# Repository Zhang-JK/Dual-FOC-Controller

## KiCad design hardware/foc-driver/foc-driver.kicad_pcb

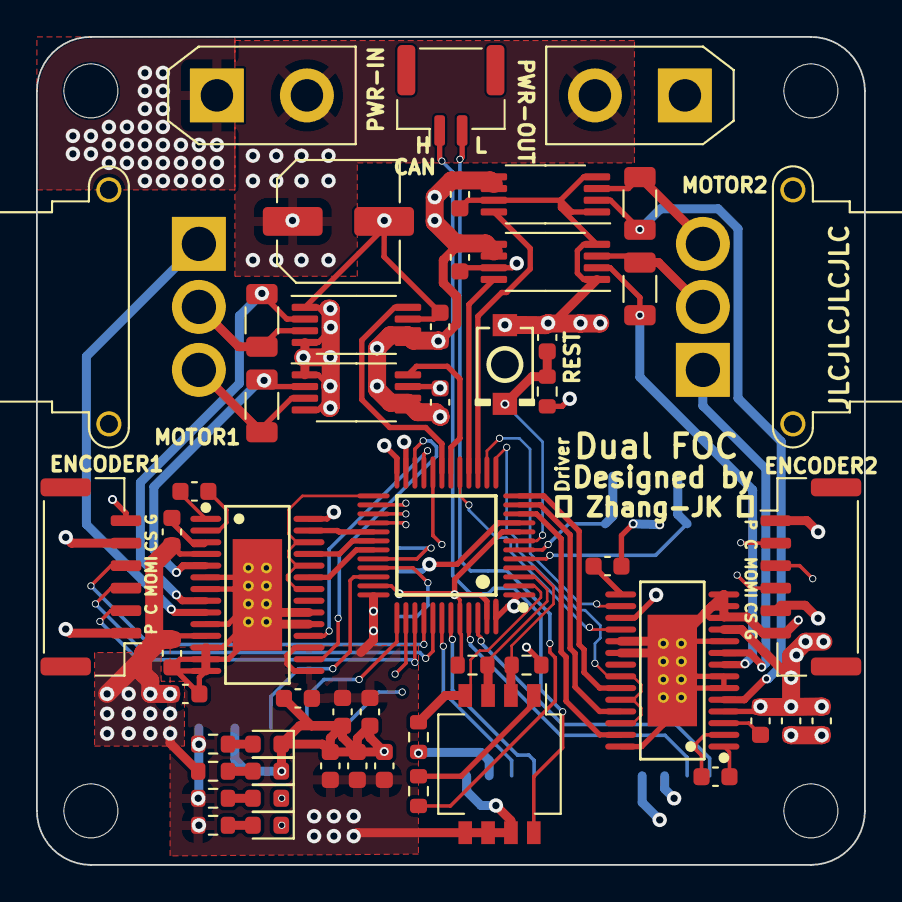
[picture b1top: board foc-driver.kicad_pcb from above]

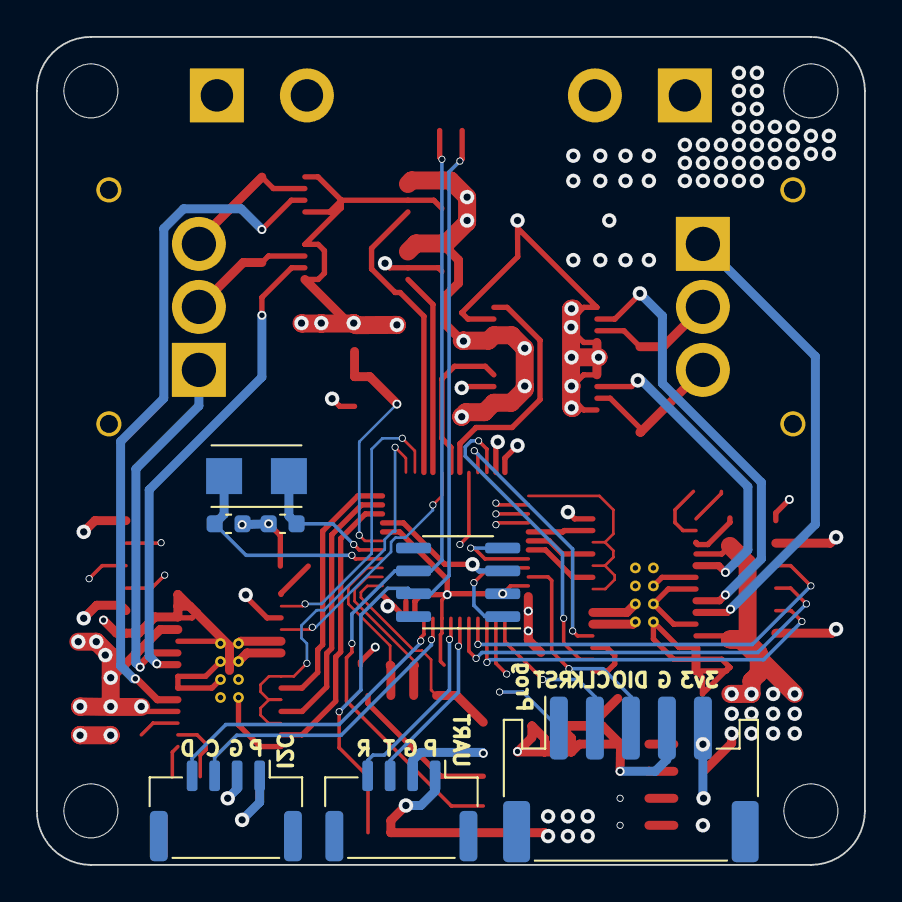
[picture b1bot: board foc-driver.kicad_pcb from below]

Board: 4 copper layers, 46.0 x 46.0 mm, 65 parts (7 on the bottom side), 65 nets.

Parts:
C1, C2, C3, C4, C7, C8, C9, C10, C12, C13, C18, C19, C20, C21: 0.1uF; C_0603_1608Metric
C5, C6: 0.01uF; C_0603_1608Metric
C11: 10uF; C_0603_1608Metric
C14, C15: 0.47uF; C_0603_1608Metric
C16, C17: 36pF; C_0603_1608Metric
C22: 100uF; C_Elec_6.3x7.7
C23: 0.1uf; C_0603_1608Metric
D2, D3: LED-R; LED_0603_1608Metric
D4: LED-B; LED_0603_1608Metric
D5: LED-G; LED_0603_1608Metric
H1, H2, H3, H4: MountingHole; MountingHole_3mm
J1: OUT1; AMASS_MR30PW-FB_1x03_P3.50mm_Horizontal
J2: OUT2; AMASS_MR30PW-FB_1x03_P3.50mm_Horizontal
J3: Encoder1; JST_GH_BM06B-GHS-TBT_1x06-1MP_P1.25mm_Vertical
J4: Encoder2; JST_GH_BM06B-GHS-TBT_1x06-1MP_P1.25mm_Vertical
J5: PWR-OUT; AMASS_XT30UPB-F_1x02_P5.0mm_Vertical
J6: PWR-IN; AMASS_XT30UPB-M_1x02_P5.0mm_Vertical
J7: CAN; JST_GH_BM02B-GHS-TBT_1x02-1MP_P1.25mm_Vertical
J9: UART; JST_GH_BM04B-GHS-TBT_1x04-1MP_P1.25mm_Vertical
J10: I2C; JST_GH_BM04B-GHS-TBT_1x04-1MP_P1.25mm_Vertical
J11: SWD; JST_PH_S5B-PH-SM4-TB_1x05-1MP_P2.00mm_Horizontal
R1, R2, R3, R4: 0.01R; R_1206_3216Metric
R8: 120R; R_0603_1608Metric
R9, R10, R11, R16: 10kR; R_0603_1608Metric
R12, R14: 10kΩ; R_0603_1608Metric
R13, R15: 2kΩ; R_0603_1608Metric
SW1: SW_DIP_x04; SW_DIP_SPSTx04_Slide_KingTek_DSHP04TS_W7.62mm_P1.27mm
SW2: Switch-Stand; SW-SMD_L3.9-W3.0-P4.45
U1, U2, U3, U4: INA240A2PW; TSSOP-8_4.4x3mm_P0.65mm
U5: STM32F103C8T6; LQFP-48_7X7X05P
U6, U7: DRV8313PWPR; HTSSOP-28_L9.8-W4.5-P0.65-LS6.6-BL-EP
U8: SN65HVD232; SOIC-8_3.9x4.9mm_P1.27mm
Y1: 8MHz 20pF; Crystal_SMD_Qantek_QC5CB-2Pin_5x3.2mm

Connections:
+3V3: C1.1, C2.1, C3.1, C4.1, C7.2, C8.2, C9.2, C10.2, C11.2, C15.1, J3.1, J3.5, J4.1, J4.5, J9.1, J10.1, J11.5, R13.1, R14.1, R15.1, R16.2, SW1.5, SW1.6, SW1.7, U1.5 (V+), U1.6 (REF2), U2.5 (V+), U2.6 (REF2), U3.5 (V+), U3.6 (REF2), U4.5 (V+), U4.6 (REF2), U5.1 (VBAT), U5.9 (VDDA), U5.24 (VDD_1), U5.36 (VDD_2), U5.48 (VDD_3), U6.15 (V3P3OUT), U6.17 (SLEEP#), U7.17 (SLEEP#), U8.3 (VCC)
+12V: C12.1, C13.1, C18.2, C19.2, C20.2, C21.2, C22.1, J5.2, J6.2, R12.1, U6.4 (VM), U6.11 (VM), U7.4 (VM), U7.11 (VM)
/ADC1_IN8: U3.8, U5.18 (PB0)
/ADC1_IN9: U1.8, U5.19 (PB1)
/ADC2_IN5: U4.8, U5.15 (PA5)
/ADC2_IN6: U2.8, U5.16 (PA6)
/CANH: J7.1, SW1.8, U8.7 (CANH)
/CANL: J7.2, R8.1, U8.6 (CANL)
/CAN_RX: U5.32 (PA11), U8.4 (R)
/CAN_TX: U5.33 (PA12), U8.1 (D)
/I2C1_SCL: J10.3, U5.45 (PB8)
/I2C1_SDA: J10.4, U5.46 (PB9)
/LED0: D5.1 (K), U5.38 (PA15)
/LED1: D4.1 (K), U5.20 (PB2)
/MOTOR_EN1: U5.25 (PB12), U6.22 (EN3), U6.24 (EN2), U6.26 (EN1)
/MOTOR_EN2: U5.13 (PA3), U7.22 (EN3), U7.24 (EN2), U7.26 (EN1)
/MOTOR_FAULT1: U5.21 (PB10), U6.18 (FAULT#)
/MOTOR_FAULT2: U5.17 (PA7), U7.18 (FAULT#)
/MOTOR_RST1: U5.22 (PB11), U6.16 (RESET#)
/MOTOR_RST2: U5.14 (PA4), U7.16 (RESET#)
/OUT1_A: J1.3, R3.2, U3.3 (-)
/OUT1_A_CS: R3.1, U3.2 (+), U6.5 (OUT1)
/OUT1_B: J1.2, R1.2, U1.3 (-)
/OUT1_B_CS: R1.1, U1.2 (+), U6.8 (OUT2)
/OUT1_C: J1.1, U6.9 (OUT3)
/OUT2_A: J2.3, R4.2, U4.3 (-)
/OUT2_A_CS: R4.1, U4.2 (+), U7.5 (OUT1)
/OUT2_B: J2.2, R2.2, U2.3 (-)
/OUT2_B_CS: R2.1, U2.2 (+), U7.8 (OUT2)
/OUT2_C: J2.1, U7.9 (OUT3)
/RCC_OSC_IN: C16.2, U5.5 (PD0-OSC_IN), Y1.1
/RCC_OSC_OUT: C17.2, U5.6 (PD1), Y1.2
/RESET: C23.2, J11.1, R16.1, SW2.2, U5.7 (NRST)
/SPI1_MISO: J3.4, U5.40 (PB4)
/SPI1_MOSI: J3.3, U5.41 (PB5)
/SPI1_SCK: J3.2, U5.39 (PB3)
/SPI2_MISO: J4.4, U5.27 (PB14)
/SPI2_MOSI: J4.3, U5.28 (PB15)
/SPI2_SCK: J4.2, U5.26 (PB13)
/SW0: R9.2, SW1.2, U5.4 (PC15-OSC32_OUT)
/SW1: R10.2, SW1.3, U5.3 (PC14-OSC32_IN)
/SW2: R11.2, SW1.4, U5.2 (PC13-TAMPER-RTC)
/SWCLK: J11.2, U5.37 (PA14)
/SWDIO: J11.3, U5.34 (PA13)
/TIM1_CH1: U5.29 (PA8), U6.27 (IN1)
/TIM1_CH2: U5.30 (PA9), U6.25 (IN2)
/TIM1_CH3: U5.31 (PA10), U6.23 (IN3)
/TIM2_CH1: U5.10 (PA0-WKUP), U7.27 (IN1)
/TIM2_CH2: U5.11 (PA1), U7.25 (IN2)
/TIM2_CH3: U5.12 (PA2), U7.23 (IN3)
/UART1_RX: J9.4, U5.43 (PB7)
/UART1_TX: J9.3, U5.42 (PB6)
GND: C1.2, C2.2, C3.2, C4.2, C7.1, C8.1, C9.1, C10.1, C11.1, C14.2, C15.2, C16.1, C17.1, C18.1, C19.1, C20.1, C21.1, C22.2, C23.1, D2.1 (K), D3.1 (K), J3.6, J4.6, J5.1, J6.1, J9.2, J10.2, J11.4, R9.1, R10.1, R11.1, SW2.1, U1.1 (GND), U1.4 (GND), U1.7 (REF1), U2.1 (GND), U2.4 (GND), U2.7 (REF1), U3.1 (GND), U3.4 (GND), U3.7 (REF1), U4.1 (GND), U4.4 (GND), U4.7 (REF1), U5.8 (VSSA), U5.23 (VSS_1), U5.35 (VSS_2), U5.44 (BOOT0), U5.47 (VSS_3), U6.6 (PGND1), U6.7 (PGND2), U6.10 (PGND3), U6.12 (COMPP), U6.13 (COMPN), U6.14 (GND), U6.19 (COMPO#), U6.20 (GND), U6.28 (GND), U6.29 (EP), U7.6 (PGND1), U7.7 (PGND2), U7.10 (PGND3), U7.12 (COMPP), U7.13 (COMPN), U7.14 (GND), U7.19 (COMPO#), U7.20 (GND), U7.28 (GND), U7.29 (EP), U8.2 (GND)
unnamed: D2.2 (A), R12.2
unnamed: D3.2 (A), R13.2
unnamed: D4.2 (A), R14.2
unnamed: D5.2 (A), R15.2
unnamed: R8.2, SW1.1
unnamed: C5.1, U6.1 (CP1)
unnamed: C5.2, U6.2 (CP2)
unnamed: C12.2, U6.3 (VCP)
unnamed: C6.1, U7.1 (CP1)
unnamed: C6.2, U7.2 (CP2)
unnamed: C14.1, U7.15 (V3P3OUT)
unnamed: C13.2, U7.3 (VCP)

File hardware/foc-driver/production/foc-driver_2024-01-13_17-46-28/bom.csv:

Designator,Footprint,Quantity,Value,LCSC Part #
"C1, C10, C12, C13, C18, C19, C2, C20, C21, C23, C3, C4, C7, C8, C9",0603,15,0.1uF,
C11,0603,1,10uF,
"C14, C15",0603,2,0.47uF,
"C16, C17",0603,2,36pF,
C22,C_Elec_6.3x7.7,1,100uF,
"C5, C6",0603,2,0.01uF,
"D2, D3",0603,2,LED-R,
D4,0603,1,LED-B,
D5,0603,1,LED-G,
"H1, H2, H3, H4",MountingHole_3mm,4,MountingHole,
J1,AMASS_MR30PW-FB_1x03_P3.50mm_Horizontal,1,OUT1,
J10,JST_GH_BM04B-GHS-TBT_1x04-1MP_P1.25mm_Vertical,1,I2C,
J11,JST_PH_S5B-PH-SM4-TB_1x05-1MP_P2.00mm_Horizontal,1,SWD,
J2,AMASS_MR30PW-FB_1x03_P3.50mm_Horizontal,1,OUT2,
J3,JST_GH_BM06B-GHS-TBT_1x06-1MP_P1.25mm_Vertical,1,Encoder1,
J4,JST_GH_BM06B-GHS-TBT_1x06-1MP_P1.25mm_Vertical,1,Encoder2,
J5,AMASS_XT30UPB-F_1x02_P5.0mm_Vertical,1,PWR-OUT,
J6,AMASS_XT30UPB-M_1x02_P5.0mm_Vertical,1,PWR-IN,
J7,JST_GH_BM02B-GHS-TBT_1x02-1MP_P1.25mm_Vertical,1,CAN,
J9,JST_GH_BM04B-GHS-TBT_1x04-1MP_P1.25mm_Vertical,1,UART,
"R1, R2, R3, R4",1206,4,0.01R,
"R10, R11, R16, R9",0603,4,10kR,
"R12, R14",0603,2,10kΩ,
"R13, R15",0603,2,2kΩ,
R8,0603,1,120R,
SW1,SW_DIP_SPSTx04_Slide_KingTek_DSHP04TS_W7.62mm_P1.27mm,1,SW_DIP_x04,
SW2,SW-SMD_L3.9-W3.0-P4.45,1,Switch-Stand,
"U1, U2, U3, U4",TSSOP-8_4.4x3mm_P0.65mm,4,INA240A2PW,
U5,LQFP-48_7X7X05P,1,STM32F103C8T6,
"U6, U7",HTSSOP-28_L9.8-W4.5-P0.65-LS6.6-BL-EP,2,DRV8313PWPR,
U8,SOIC-8_3.9x4.9mm_P1.27mm,1,SN65HVD232,
Y1,Crystal_SMD_Qantek_QC5CB-2Pin_5x3.2mm,1,8MHz 20pF,

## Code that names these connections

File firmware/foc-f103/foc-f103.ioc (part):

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Mcu.Name=STM32F103C(8-B)Tx
Mcu.Package=LQFP48
Mcu.UserName=STM32F103C8Tx
PA0-WKUP.Signal=S_TIM2_CH1_ETR
PA1.Signal=S_TIM2_CH2
PA10.Signal=S_TIM1_CH3
PA11.Mode=CAN_Activate
PA11.Signal=CAN_RX
PA12.Mode=CAN_Activate
PA12.Signal=CAN_TX
PA13.Mode=Serial_Wire
PA13.Signal=SYS_JTMS-SWDIO
PA14.Mode=Serial_Wire
PA14.Signal=SYS_JTCK-SWCLK
PA15.GPIOParameters=GPIO_Label
PA15.GPIO_Label=LED0
PA15.Signal=GPIO_Output
PA2.Signal=S_TIM2_CH3
PA3.GPIOParameters=GPIO_Label
PA3.GPIO_Label=MOTOR_EN2
PA3.Signal=GPIO_Output
PA4.GPIOParameters=GPIO_Label
PA4.GPIO_Label=MOTOR_RST2
PA4.Signal=GPIO_Output
PA5.Signal=ADCx_IN5
PA6.Signal=ADCx_IN6
PA7.GPIOParameters=GPIO_Label
PA7.GPIO_Label=MOTOR_FAULT2
PA7.Signal=GPIO_Input
PA8.Signal=S_TIM1_CH1
PA9.Signal=S_TIM1_CH2
PB0.Signal=ADCx_IN8
PB1.Signal=ADCx_IN9
PB10.GPIOParameters=GPIO_Label
PB10.GPIO_Label=MOTOR_FAULT1
PB10.Signal=GPIO_Input
PB11.GPIOParameters=GPIO_Label
PB11.GPIO_Label=MOTOR_RST1
PB11.Signal=GPIO_Output
PB12.GPIOParameters=GPIO_Label
PB12.GPIO_Label=MOTOR_EN1
PB12.Signal=GPIO_Output
PB13.Mode=Full_Duplex_Master
PB13.Signal=SPI2_SCK
PB14.Mode=Full_Duplex_Master
PB14.Signal=SPI2_MISO
PB15.Mode=Full_Duplex_Master
PB15.Signal=SPI2_MOSI
PB2.GPIOParameters=GPIO_Label
PB2.GPIO_Label=LED1
PB2.Signal=GPIO_Output
PB3.Mode=Full_Duplex_Master
PB3.Signal=SPI1_SCK
PB4.Mode=Full_Duplex_Master
PB4.Signal=SPI1_MISO
PB5.Mode=Full_Duplex_Master
PB5.Signal=SPI1_MOSI
PB6.Mode=Asynchronous
PB6.Signal=USART1_TX
PB7.Mode=Asynchronous
PB7.Signal=USART1_RX
PB8.Mode=I2C
PB8.Signal=I2C1_SCL
PB9.Mode=I2C
PB9.Signal=I2C1_SDA
PC13-TAMPER-RTC.GPIOParameters=GPIO_Label
PC13-TAMPER-RTC.GPIO_Label=SW2
PC13-TAMPER-RTC.Signal=GPIO_Input
PC14-OSC32_IN.GPIOParameters=GPIO_Label
PC14-OSC32_IN.GPIO_Label=SW1
PC14-OSC32_IN.Signal=GPIO_Input
PC15-OSC32_OUT.GPIOParameters=GPIO_Label
PC15-OSC32_OUT.GPIO_Label=SW0
PC15-OSC32_OUT.Signal=GPIO_Input
PD0-OSC_IN.Mode=HSE-External-Oscillator
PD0-OSC_IN.Signal=RCC_OSC_IN
PD1-OSC_OUT.Mode=HSE-External-Oscillator
PD1-OSC_OUT.Signal=RCC_OSC_OUT
board=custom

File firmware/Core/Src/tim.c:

/* USER CODE BEGIN Header */
/**
  ******************************************************************************
  * @file    tim.c
  * @brief   This file provides code for the configuration
  *          of the TIM instances.
  ******************************************************************************
  * @attention
  *
  * Copyright (c) 2024 STMicroelectronics.
  * All rights reserved.
  *
  * This software is licensed under terms that can be found in the LICENSE file
  * in the root directory of this software component.
  * If no LICENSE file comes with this software, it is provided AS-IS.
  *
  ******************************************************************************
  */
/* USER CODE END Header */
/* Includes ------------------------------------------------------------------*/
#include "tim.h"

/* USER CODE BEGIN 0 */

/* USER CODE END 0 */

TIM_HandleTypeDef htim1;
TIM_HandleTypeDef htim2;

/* TIM1 init function */
void MX_TIM1_Init(void)
{

  /* USER CODE BEGIN TIM1_Init 0 */

  /* USER CODE END TIM1_Init 0 */

  TIM_MasterConfigTypeDef sMasterConfig = {0};
  TIM_OC_InitTypeDef sConfigOC = {0};
  TIM_BreakDeadTimeConfigTypeDef sBreakDeadTimeConfig = {0};

  /* USER CODE BEGIN TIM1_Init 1 */

  /* USER CODE END TIM1_Init 1 */
  htim1.Instance = TIM1;
  htim1.Init.Prescaler = 0;
  htim1.Init.CounterMode = TIM_COUNTERMODE_UP;
  htim1.Init.Period = 65535;
  htim1.Init.ClockDivision = TIM_CLOCKDIVISION_DIV1;
  htim1.Init.RepetitionCounter = 0;
  htim1.Init.AutoReloadPreload = TIM_AUTORELOAD_PRELOAD_DISABLE;
  if (HAL_TIM_PWM_Init(&htim1) != HAL_OK)
  {
    Error_Handler();
  }
  if (HAL_TIM_OC_Init(&htim1) != HAL_OK)
  {
    Error_Handler();
  }
  sMasterConfig.MasterOutputTrigger = TIM_TRGO_RESET;
  sMasterConfig.MasterSlaveMode = TIM_MASTERSLAVEMODE_DISABLE;
  if (HAL_TIMEx_MasterConfigSynchronization(&htim1, &sMasterConfig) != HAL_OK)
  {
    Error_Handler();
  }
  sConfigOC.OCMode = TIM_OCMODE_PWM1;
  sConfigOC.Pulse = 0;
  sConfigOC.OCPolarity = TIM_OCPOLARITY_HIGH;
  sConfigOC.OCNPolarity = TIM_OCNPOLARITY_HIGH;
  sConfigOC.OCFastMode = TIM_OCFAST_DISABLE;
  sConfigOC.OCIdleState = TIM_OCIDLESTATE_RESET;
  sConfigOC.OCNIdleState = TIM_OCNIDLESTATE_RESET;
  if (HAL_TIM_PWM_ConfigChannel(&htim1, &sConfigOC, TIM_CHANNEL_1) != HAL_OK)
  {
    Error_Handler();
  }
  sConfigOC.OCMode = TIM_OCMODE_TIMING;
  if (HAL_TIM_OC_ConfigChannel(&htim1, &sConfigOC, TIM_CHANNEL_2) != HAL_OK)
  {
    Error_Handler();
  }
  if (HAL_TIM_OC_ConfigChannel(&htim1, &sConfigOC, TIM_CHANNEL_3) != HAL_OK)
  {
    Error_Handler();
  }
  sBreakDeadTimeConfig.OffStateRunMode = TIM_OSSR_DISABLE;
  sBreakDeadTimeConfig.OffStateIDLEMode = TIM_OSSI_DISABLE;
  sBreakDeadTimeConfig.LockLevel = TIM_LOCKLEVEL_OFF;
  sBreakDeadTimeConfig.DeadTime = 0;
  sBreakDeadTimeConfig.BreakState = TIM_BREAK_DISABLE;
  sBreakDeadTimeConfig.BreakPolarity = TIM_BREAKPOLARITY_HIGH;
  sBreakDeadTimeConfig.AutomaticOutput = TIM_AUTOMATICOUTPUT_DISABLE;
  if (HAL_TIMEx_ConfigBreakDeadTime(&htim1, &sBreakDeadTimeConfig) != HAL_OK)
  {
    Error_Handler();
  }
  /* USER CODE BEGIN TIM1_Init 2 */

  /* USER CODE END TIM1_Init 2 */
  HAL_TIM_MspPostInit(&htim1);

}
/* TIM2 init function */
void MX_TIM2_Init(void)
{

  /* USER CODE BEGIN TIM2_Init 0 */

  /* USER CODE END TIM2_Init 0 */

  TIM_MasterConfigTypeDef sMasterConfig = {0};
  TIM_OC_InitTypeDef sConfigOC = {0};

  /* USER CODE BEGIN TIM2_Init 1 */

  /* USER CODE END TIM2_Init 1 */
  htim2.Instance = TIM2;
  htim2.Init.Prescaler = 0;
  htim2.Init.CounterMode = TIM_COUNTERMODE_UP;
  htim2.Init.Period = 65535;
  htim2.Init.ClockDivision = TIM_CLOCKDIVISION_DIV1;
  htim2.Init.AutoReloadPreload = TIM_AUTORELOAD_PRELOAD_DISABLE;
  if (HAL_TIM_PWM_Init(&htim2) != HAL_OK)
  {
    Error_Handler();
  }
  sMasterConfig.MasterOutputTrigger = TIM_TRGO_RESET;
  sMasterConfig.MasterSlaveMode = TIM_MASTERSLAVEMODE_DISABLE;
  if (HAL_TIMEx_MasterConfigSynchronization(&htim2, &sMasterConfig) != HAL_OK)
  {
    Error_Handler();
  }
  sConfigOC.OCMode = TIM_OCMODE_PWM1;
  sConfigOC.Pulse = 0;
  sConfigOC.OCPolarity = TIM_OCPOLARITY_HIGH;
  sConfigOC.OCFastMode = TIM_OCFAST_DISABLE;
  if (HAL_TIM_PWM_ConfigChannel(&htim2, &sConfigOC, TIM_CHANNEL_1) != HAL_OK)
  {
    Error_Handler();
  }
  if (HAL_TIM_PWM_ConfigChannel(&htim2, &sConfigOC, TIM_CHANNEL_2) != HAL_OK)
  {
    Error_Handler();
  }
  if (HAL_TIM_PWM_ConfigChannel(&htim2, &sConfigOC, TIM_CHANNEL_3) != HAL_OK)
  {
    Error_Handler();
  }
  /* USER CODE BEGIN TIM2_Init 2 */

  /* USER CODE END TIM2_Init 2 */
  HAL_TIM_MspPostInit(&htim2);

}

void HAL_TIM_PWM_MspInit(TIM_HandleTypeDef* tim_pwmHandle)
{

  if(tim_pwmHandle->Instance==TIM1)
  {
  /* USER CODE BEGIN TIM1_MspInit 0 */

  /* USER CODE END TIM1_MspInit 0 */
    /* TIM1 clock enable */
    __HAL_RCC_TIM1_CLK_ENABLE();
  /* USER CODE BEGIN TIM1_MspInit 1 */

  /* USER CODE END TIM1_MspInit 1 */
  }
  else if(tim_pwmHandle->Instance==TIM2)
  {
  /* USER CODE BEGIN TIM2_MspInit 0 */

  /* USER CODE END TIM2_MspInit 0 */
    /* TIM2 clock enable */
    __HAL_RCC_TIM2_CLK_ENABLE();
  /* USER CODE BEGIN TIM2_MspInit 1 */

  /* USER CODE END TIM2_MspInit 1 */
  }
}
void HAL_TIM_MspPostInit(TIM_HandleTypeDef* timHandle)
{

  GPIO_InitTypeDef GPIO_InitStruct = {0};
  if(timHandle->Instance==TIM1)
  {
  /* USER CODE BEGIN TIM1_MspPostInit 0 */

  /* USER CODE END TIM1_MspPostInit 0 */
    __HAL_RCC_GPIOA_CLK_ENABLE();
    /**TIM1 GPIO Configuration
    PA8     ------> TIM1_CH1
    PA9     ------> TIM1_CH2
    PA10     ------> TIM1_CH3
    */
    GPIO_InitStruct.Pin = GPIO_PIN_8|GPIO_PIN_9|GPIO_PIN_10;
    GPIO_InitStruct.Mode = GPIO_MODE_AF_PP;
    GPIO_InitStruct.Speed = GPIO_SPEED_FREQ_LOW;
    HAL_GPIO_Init(GPIOA, &GPIO_InitStruct);

  /* USER CODE BEGIN TIM1_MspPostInit 1 */

  /* USER CODE END TIM1_MspPostInit 1 */
  }
  else if(timHandle->Instance==TIM2)
  {
  /* USER CODE BEGIN TIM2_MspPostInit 0 */

  /* USER CODE END TIM2_MspPostInit 0 */

    __HAL_RCC_GPIOA_CLK_ENABLE();
    /**TIM2 GPIO Configuration
    PA0-WKUP     ------> TIM2_CH1
    PA1     ------> TIM2_CH2
    PA2     ------> TIM2_CH3
    */
    GPIO_InitStruct.Pin = GPIO_PIN_0|GPIO_PIN_1|GPIO_PIN_2;
    GPIO_InitStruct.Mode = GPIO_MODE_AF_PP;
    GPIO_InitStruct.Speed = GPIO_SPEED_FREQ_LOW;
    HAL_GPIO_Init(GPIOA, &GPIO_InitStruct);

  /* USER CODE BEGIN TIM2_MspPostInit 1 */

  /* USER CODE END TIM2_MspPostInit 1 */
  }

}

void HAL_TIM_PWM_MspDeInit(TIM_HandleTypeDef* tim_pwmHandle)
{

  if(tim_pwmHandle->Instance==TIM1)
  {
  /* USER CODE BEGIN TIM1_MspDeInit 0 */

  /* USER CODE END TIM1_MspDeInit 0 */
    /* Peripheral clock disable */
    __HAL_RCC_TIM1_CLK_DISABLE();
  /* USER CODE BEGIN TIM1_MspDeInit 1 */

  /* USER CODE END TIM1_MspDeInit 1 */
  }
  else if(tim_pwmHandle->Instance==TIM2)
  {
  /* USER CODE BEGIN TIM2_MspDeInit 0 */

  /* USER CODE END TIM2_MspDeInit 0 */
    /* Peripheral clock disable */
    __HAL_RCC_TIM2_CLK_DISABLE();
  /* USER CODE BEGIN TIM2_MspDeInit 1 */

  /* USER CODE END TIM2_MspDeInit 1 */
  }
}

/* USER CODE BEGIN 1 */

/* USER CODE END 1 */

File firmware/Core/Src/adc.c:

/* USER CODE BEGIN Header */
/**
  ******************************************************************************
  * @file    adc.c
  * @brief   This file provides code for the configuration
  *          of the ADC instances.
  ******************************************************************************
  * @attention
  *
  * Copyright (c) 2024 STMicroelectronics.
  * All rights reserved.
  *
  * This software is licensed under terms that can be found in the LICENSE file
  * in the root directory of this software component.
  * If no LICENSE file comes with this software, it is provided AS-IS.
  *
  ******************************************************************************
  */
/* USER CODE END Header */
/* Includes ------------------------------------------------------------------*/
#include "adc.h"

/* USER CODE BEGIN 0 */

/* USER CODE END 0 */

ADC_HandleTypeDef hadc1;
ADC_HandleTypeDef hadc2;

/* ADC1 init function */
void MX_ADC1_Init(void)
{

  /* USER CODE BEGIN ADC1_Init 0 */

  /* USER CODE END ADC1_Init 0 */

  ADC_ChannelConfTypeDef sConfig = {0};

  /* USER CODE BEGIN ADC1_Init 1 */

  /* USER CODE END ADC1_Init 1 */

  /** Common config
  */
  hadc1.Instance = ADC1;
  hadc1.Init.ScanConvMode = ADC_SCAN_DISABLE;
  hadc1.Init.ContinuousConvMode = DISABLE;
  hadc1.Init.DiscontinuousConvMode = DISABLE;
  hadc1.Init.ExternalTrigConv = ADC_SOFTWARE_START;
  hadc1.Init.DataAlign = ADC_DATAALIGN_RIGHT;
  hadc1.Init.NbrOfConversion = 1;
  if (HAL_ADC_Init(&hadc1) != HAL_OK)
  {
    Error_Handler();
  }

  /** Configure Regular Channel
  */
  sConfig.Channel = ADC_CHANNEL_8;
  sConfig.Rank = ADC_REGULAR_RANK_1;
  sConfig.SamplingTime = ADC_SAMPLETIME_1CYCLE_5;
  if (HAL_ADC_ConfigChannel(&hadc1, &sConfig) != HAL_OK)
  {
    Error_Handler();
  }
  /* USER CODE BEGIN ADC1_Init 2 */

  /* USER CODE END ADC1_Init 2 */

}
/* ADC2 init function */
void MX_ADC2_Init(void)
{

  /* USER CODE BEGIN ADC2_Init 0 */

  /* USER CODE END ADC2_Init 0 */

  ADC_ChannelConfTypeDef sConfig = {0};

  /* USER CODE BEGIN ADC2_Init 1 */

  /* USER CODE END ADC2_Init 1 */

  /** Common config
  */
  hadc2.Instance = ADC2;
  hadc2.Init.ScanConvMode = ADC_SCAN_DISABLE;
  hadc2.Init.ContinuousConvMode = DISABLE;
  hadc2.Init.DiscontinuousConvMode = DISABLE;
  hadc2.Init.ExternalTrigConv = ADC_SOFTWARE_START;
  hadc2.Init.DataAlign = ADC_DATAALIGN_RIGHT;
  hadc2.Init.NbrOfConversion = 1;
  if (HAL_ADC_Init(&hadc2) != HAL_OK)
  {
    Error_Handler();
  }

  /** Configure Regular Channel
  */
  sConfig.Channel = ADC_CHANNEL_5;
  sConfig.Rank = ADC_REGULAR_RANK_1;
  sConfig.SamplingTime = ADC_SAMPLETIME_1CYCLE_5;
  if (HAL_ADC_ConfigChannel(&hadc2, &sConfig) != HAL_OK)
  {
    Error_Handler();
  }
  /* USER CODE BEGIN ADC2_Init 2 */

  /* USER CODE END ADC2_Init 2 */

}

void HAL_ADC_MspInit(ADC_HandleTypeDef* adcHandle)
{

  GPIO_InitTypeDef GPIO_InitStruct = {0};
  if(adcHandle->Instance==ADC1)
  {
  /* USER CODE BEGIN ADC1_MspInit 0 */

  /* USER CODE END ADC1_MspInit 0 */
    /* ADC1 clock enable */
    __HAL_RCC_ADC1_CLK_ENABLE();

    __HAL_RCC_GPIOB_CLK_ENABLE();
    /**ADC1 GPIO Configuration
    PB0     ------> ADC1_IN8
    PB1     ------> ADC1_IN9
    */
    GPIO_InitStruct.Pin = GPIO_PIN_0|GPIO_PIN_1;
    GPIO_InitStruct.Mode = GPIO_MODE_ANALOG;
    HAL_GPIO_Init(GPIOB, &GPIO_InitStruct);

  /* USER CODE BEGIN ADC1_MspInit 1 */

  /* USER CODE END ADC1_MspInit 1 */
  }
  else if(adcHandle->Instance==ADC2)
  {
  /* USER CODE BEGIN ADC2_MspInit 0 */

  /* USER CODE END ADC2_MspInit 0 */
    /* ADC2 clock enable */
    __HAL_RCC_ADC2_CLK_ENABLE();

    __HAL_RCC_GPIOA_CLK_ENABLE();
    /**ADC2 GPIO Configuration
    PA5     ------> ADC2_IN5
    PA6     ------> ADC2_IN6
    */
    GPIO_InitStruct.Pin = GPIO_PIN_5|GPIO_PIN_6;
    GPIO_InitStruct.Mode = GPIO_MODE_ANALOG;
    HAL_GPIO_Init(GPIOA, &GPIO_InitStruct);

  /* USER CODE BEGIN ADC2_MspInit 1 */

  /* USER CODE END ADC2_MspInit 1 */
  }
}

void HAL_ADC_MspDeInit(ADC_HandleTypeDef* adcHandle)
{

  if(adcHandle->Instance==ADC1)
  {
  /* USER CODE BEGIN ADC1_MspDeInit 0 */

  /* USER CODE END ADC1_MspDeInit 0 */
    /* Peripheral clock disable */
    __HAL_RCC_ADC1_CLK_DISABLE();

    /**ADC1 GPIO Configuration
    PB0     ------> ADC1_IN8
    PB1     ------> ADC1_IN9
    */
    HAL_GPIO_DeInit(GPIOB, GPIO_PIN_0|GPIO_PIN_1);

  /* USER CODE BEGIN ADC1_MspDeInit 1 */

  /* USER CODE END ADC1_MspDeInit 1 */
  }
  else if(adcHandle->Instance==ADC2)
  {
  /* USER CODE BEGIN ADC2_MspDeInit 0 */

  /* USER CODE END ADC2_MspDeInit 0 */
    /* Peripheral clock disable */
    __HAL_RCC_ADC2_CLK_DISABLE();

    /**ADC2 GPIO Configuration
    PA5     ------> ADC2_IN5
    PA6     ------> ADC2_IN6
    */
    HAL_GPIO_DeInit(GPIOA, GPIO_PIN_5|GPIO_PIN_6);

  /* USER CODE BEGIN ADC2_MspDeInit 1 */

  /* USER CODE END ADC2_MspDeInit 1 */
  }
}

/* USER CODE BEGIN 1 */

/* USER CODE END 1 */

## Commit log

2024-01-20 finish first version of hardware design
2024-01-20 add git ignore
2024-01-24 port to cmake project with freertos
2024-01-24 add freertos as submodule
2024-01-25 freertos porting; cross compile with c++
2024-01-25 freertos running successfully
